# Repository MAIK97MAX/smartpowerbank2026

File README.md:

# Semesterproject 2026 - Smart Powerbank

## Authors
Jukic Malik & Sayfutdinov David - HTL Rankweil

## Goal 
The goal of this project is to design and build a smart power bank with USB-C charging, battery management and system monitoring.

## Features
- USB-C charging
- OLED display for battery status and system information
- ESP8266 module for web interface
- Battery monitoring and protection

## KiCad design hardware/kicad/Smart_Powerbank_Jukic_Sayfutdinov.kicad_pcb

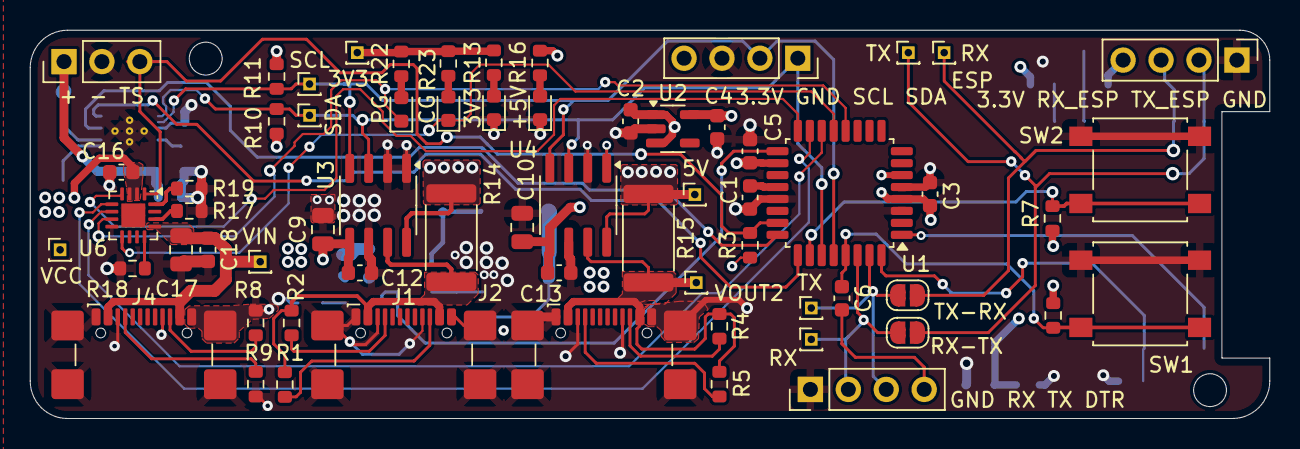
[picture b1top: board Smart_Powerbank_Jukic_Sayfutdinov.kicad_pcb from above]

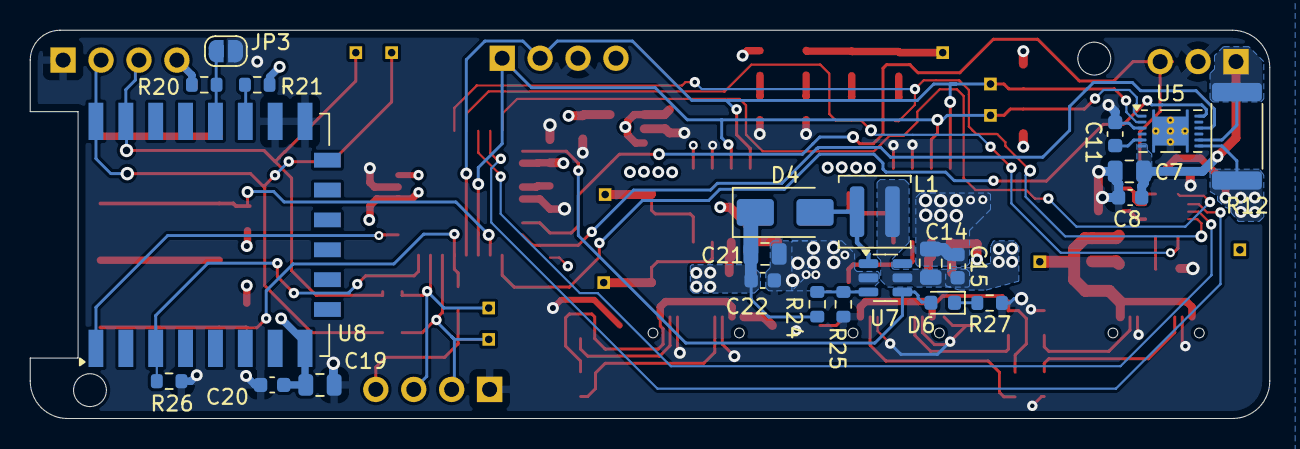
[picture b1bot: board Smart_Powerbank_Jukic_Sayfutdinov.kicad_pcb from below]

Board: 4 copper layers, 83.0 x 26.0 mm, 87 parts (23 on the bottom side), 48 nets.

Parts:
3.3V GND SCL SDA: Conn_01x04_Pin; PinSocket_1x04_P2.54mm_Vertical
3.3V RX_ESP TX_ESP GND: Conn_01x04_Pin; PinHeader_1x04_P2.54mm_Vertical
3V3: LED; LED_0603_1608Metric
3V3#2, 5V: TestPoint_Probe; PinHeader_1x01_P1.00mm_Vertical
+5V: LED; LED_0603_1608Metric
+ - TS: Conn_01x03_Pin; PinHeader_1x03_P2.54mm_Vertical
C1, C2, C3, C4, C5, C6, C8, C12, C13, C15, C18, C20, C22: 100nF; C_0603_1608Metric
C7, C17: 1uF; C_0805_2012Metric
C9, C10, C19: 10uF; C_0805_2012Metric
C11: 470nF; C_0603_1608Metric
C14, C21: 22uF; C_0805_2012Metric
C16: 4.7uF; C_0603_1608Metric
CG: LED; LED_0603_1608Metric
D4: D_Schottky; D_SMA
D6: n.b.; LED_0603_1608Metric
GND RX TX DTR: Conn_01x04_Pin; PinHeader_1x04_P2.54mm_Vertical
J1, J2, J4: USB_C_Receptacle_USB2.0_16P; USB_C_Receptacle_GCT_USB4110
JP3: SolderJumper_2_Open; SolderJumper-2_P1.3mm_Open_RoundedPad1.0x1.5mm
L1: 4.7uH; L_Coilcraft_XAL4030-XXX
PG: LED; LED_0603_1608Metric
R1, R2, R3, R4, R5, R6, R7, R20, R21: 10k; R_0603_1608Metric
R8, R9: 5k1; R_0603_1608Metric
R10, R11: 3.3k; R_0603_1608Metric
R12, R14, R15: 0.01; R_2512_6332Metric
R13, R16, R18, R19, R22, R23: 1k; R_0603_1608Metric
R17: 47k; R_0603_1608Metric
R24: 110k; R_0603_1608Metric
R25: 15k; R_0603_1608Metric
R26: 100k; R_0603_1608Metric
R27: n.b.; R_0603_1608Metric
RX: TestPoint_Probe; PinHeader_1x01_P1.00mm_Vertical
RX#2: TestPoint_Probe; PinHeader_1x01_P1.00mm_Vertical
RX-TX: SolderJumper_2_Open; SolderJumper-2_P1.3mm_Open_RoundedPad1.0x1.5mm
SCL: TestPoint_Probe; PinHeader_1x01_P1.00mm_Vertical
SDA: TestPoint_Probe; PinHeader_1x01_P1.00mm_Vertical
SW1, SW2: SW_Push; SW_SPST_B3S-1000
TX: TestPoint_Probe; PinHeader_1x01_P1.00mm_Vertical
TX#2: TestPoint_Probe; PinHeader_1x01_P1.00mm_Vertical
TX-RX: SolderJumper_2_Open; SolderJumper-2_P1.3mm_Open_RoundedPad1.0x1.5mm
U1: ATmega328-A; TQFP-32_7x7mm_P0.8mm
U2: AP2112K-3.3; SOT-23-5
U3, U4: INA219AxD; SOIC-8_3.9x4.9mm_P1.27mm
U5: BQ27441-G1; Texas_S-PDSO-N12
U6: BQ24074RGT; VQFN-16-1EP_3x3mm_P0.5mm_EP1.6x1.6mm
U7: MT3608; SOT-23-6
U8: ESP-12E
VCC: TestPoint_Probe; PinHeader_1x01_P1.00mm_Vertical
VIN: TestPoint_Probe; PinHeader_1x01_P1.00mm_Vertical
VOUT2: TestPoint_Probe; PinHeader_1x01_P1.00mm_Vertical

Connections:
+3.3V: 3.3V GND SCL SDA.4, 3.3V RX_ESP TX_ESP GND.4, 3V3#2.1, C3.1, C4.1, C5.1, C9.1, C10.1, C12.1, C13.1, C19.1, C20.1, R3.2, R6.2, R7.2, R10.1, R11.1, R13.2, R20.2, R21.2, R22.2, R23.2, U1.4 (VCC), U1.6 (VCC), U1.18 (AVCC), U2.5 (VOUT), U3.5 (VS), U4.1 (A1), U4.5 (VS), U8.8 (VCC)
+5V: 5V.1, C21.1, C22.1, D4.1 (K), R14.1, R15.1, R16.2, R24.1, U3.8 (IN+), U4.8 (IN+)
/AREF: C1.1, U1.20 (AREF)
/BAT+: + - TS.1, C7.1, C8.1, R12.1, U5.6 (BAT), U5.8 (SRP)
/BIN: U1.24 (PC1), U5.10 (BIN)
/CE: U1.16 (PB4), U6.4 (~CE)
/CHG: CG.1 (K), U1.13 (PB1), U6.9 (~CHG)
/DTR: C6.2, GND RX TX DTR.4
/EN1: U1.14 (PB2), U6.6 (EN1)
/EN2: U1.15 (PB3), U6.5 (EN2)
/EN_OUT: D6.2 (A), U1.17 (PB5), U7.4 (EN)
/ESP_EN: R26.1, U1.32 (PD2), U8.3 (EN)
/ESP_RST: U1.1 (PD3), U8.1 (~RST)
/FB: R24.2, R25.1, U7.3 (FB)
/GPOUT: U1.25 (PC2), U5.12 (GPOUT)
/ILIM: R18.2, U6.12 (ILIM)
/ISET: R19.1, U6.16 (ISET)
/PGOOD: PG.1 (K), U1.12 (PB0), U6.7 (~PGOOD)
/RST: C6.1, R6.1, SW1.1, U1.29 (~RESET/PC6)
/RX: GND RX TX DTR.2, RX.1, RX-TX.1 (A), U1.30 (PD0)
/RX_ESP: 3.3V RX_ESP TX_ESP GND.3, RX#2.1, TX-RX.2 (B), U8.21 (GPIO3/RXD)
/SCL: 3.3V GND SCL SDA.2, R11.2, SCL.1, U1.28 (PC5), U3.4 (SCL), U4.4 (SCL), U5.2 (SCL)
/SDA: 3.3V GND SCL SDA.1, R10.2, SDA.1, U1.27 (PC4), U3.3 (SDA), U4.3 (SDA), U5.1 (SDA)
/SW: D4.2 (A), L1.2, U7.1 (SW)
/SW_MODE: R7.1, SW2.1, U1.26 (PC3)
/TMR: R17.2, U6.14 (TMR)
/TS: + - TS.3, R3.1, U1.23 (PC0), U6.1 (TS)
/TX: GND RX TX DTR.3, TX#2.1, TX-RX.1 (A), U1.31 (PD1)
/TX_ESP: 3.3V RX_ESP TX_ESP GND.2, RX-TX.2 (B), TX.1, U8.22 (GPIO1/TXD)
/VDD: C11.1, U5.5 (V_{DD})
GND: 3.3V GND SCL SDA.3, 3.3V RX_ESP TX_ESP GND.1, 3V3.1 (K), +5V.1 (K), + - TS.2, C1.2, C2.2, C3.2, C4.2, C5.2, C7.2, C8.2, C9.2, C10.2, C11.2, C12.2, C13.2, C14.2, C15.2, C16.1, C17.2, C18.2, C19.2, C20.2, C21.2, C22.2, GND RX TX DTR.1, J1.A1 (GND), J1.A8 (SBU1), J1.A12 (GND), J1.B1 (GND), J1.B8 (SBU2), J1.B12 (GND), J1.S1 (SHIELD), J2.A1 (GND), J2.A8 (SBU1), J2.A12 (GND), J2.B1 (GND), J2.B8 (SBU2), J2.B12 (GND), J2.S1 (SHIELD), J4.A1 (GND), J4.A8 (SBU1), J4.A12 (GND), J4.B1 (GND), J4.B8 (SBU2), J4.B12 (GND), J4.S1 (SHIELD), JP3.1 (A), R8.1, R9.2, R17.1, R18.1, R19.2, R25.2, R26.2, R27.1, SW1.2, SW2.2, U1.3 (GND), U1.5 (GND), U1.21 (GND), U2.2 (GND), U3.1 (A1), U3.2 (A0), U3.6 (GND), U4.2 (A0), U4.6 (GND), U5.3 (V_{SS}), U5.13 (PAD), U6.8 (VSS), U6.17 (VSS), U7.2 (GND), U8.15 (GND), U8.16 (GPIO15)
unnamed: 3V3.2 (A), R13.1
unnamed: +5V.2 (A), R16.1
unnamed: PG.2 (A), R22.1
unnamed: CG.2 (A), R23.1
unnamed: D6.1 (K), R27.2
unnamed: J1.A5 (CC1), R2.1
unnamed: J1.B5 (CC2), R1.2
unnamed: J2.A5 (CC1), R5.1
unnamed: J2.B5 (CC2), R4.2
unnamed: J4.A5 (CC1), R9.1
unnamed: J4.B5 (CC2), R8.2
unnamed: JP3.2 (B), R20.1, U8.18 (GPIO0)
unnamed: R21.1, U8.17 (GPIO2)
VCC: C2.1, C14.1, C15.1, C16.2, L1.1, R12.2, U2.1 (VIN), U2.3 (EN), U5.7 (SRN), U6.2 (BAT), U6.3 (BAT), U7.5 (IN), VCC.1
VIN_USB: C17.1, C18.1, J4.A4 (VBUS), J4.A9 (VBUS), J4.B4 (VBUS), J4.B9 (VBUS), U6.13 (IN), VIN.1
VOUT1: J1.A4 (VBUS), J1.A9 (VBUS), J1.B4 (VBUS), J1.B9 (VBUS), R1.1, R2.2, R14.2, U3.7 (IN-)
VOUT2: J2.A4 (VBUS), J2.A9 (VBUS), J2.B4 (VBUS), J2.B9 (VBUS), R4.1, R5.2, R15.2, U4.7 (IN-), VOUT2.1

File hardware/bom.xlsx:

Reference | Qty | Value | Footprint
C1,C2,C3,C4,C5,C6,C8,C12,C13,C15,C18,C20,C22 | 13 | 100nF | Capacitor_SMD:C_0603_1608Metric
C7,C17 | 2 | 1uF | Capacitor_SMD:C_0805_2012Metric
C9,C10,C19 | 3 | 10uF | Capacitor_SMD:C_0805_2012Metric
C11 | 1 | 470nF | Capacitor_SMD:C_0603_1608Metric
C14,C21 | 2 | 22uF | Capacitor_SMD:C_0805_2012Metric
C16 | 1 | 4.7uF | Capacitor_SMD:C_0603_1608Metric
D1,D2,D3,D5 | 4 | LED | LED_SMD:LED_0603_1608Metric
D4 | 1 | D_Schottky | Diode_SMD:D_SMA
D6 | 1 | n.b. | LED_SMD:LED_0603_1608Metric
J1,J2,J4 | 3 | USB_C_Receptacle_USB2.0_16P | Connector_USB:USB_C_Receptacle_GCT_USB4110
J3,J7 | 2 | Conn_01x04_Pin | Connector_PinHeader_2.54mm:PinHeader_1x04_P2.54mm_Vertical
J5 | 1 | Conn_01x04_Pin | Connector_PinSocket_2.54mm:PinSocket_1x04_P2.54mm_Vertical
J6 | 1 | Conn_01x03_Pin | Connector_PinHeader_2.54mm:PinHeader_1x03_P2.54mm_Vertical
JP1,JP2,JP3 | 3 | SolderJumper_2_Open | Jumper:SolderJumper-2_P1.3mm_Open_RoundedPad1.0x1.5mm
L1 | 1 | 4.7uH | Inductor_SMD:L_Coilcraft_XAL4030-XXX
R1,R2,R3,R4,R5,R6,R7,R20,R21 | 9 | 10k | Resistor_SMD:R_0603_1608Metric
R8,R9 | 2 | 5k1 | Resistor_SMD:R_0603_1608Metric
R10,R11 | 2 | 3.3k | Resistor_SMD:R_0603_1608Metric
R12,R14,R15 | 3 | 0.01 | Resistor_SMD:R_2512_6332Metric
R13,R16,R18,R19,R22,R23 | 6 | 1k | Resistor_SMD:R_0603_1608Metric
R17 | 1 | 47k | Resistor_SMD:R_0603_1608Metric
R24 | 1 | 110k | Resistor_SMD:R_0603_1608Metric
R25 | 1 | 15k | Resistor_SMD:R_0603_1608Metric
R26 | 1 | 100k | Resistor_SMD:R_0603_1608Metric
R27 | 1 | n.b. | Resistor_SMD:R_0603_1608Metric
SW1,SW2 | 2 | SW_Push | Button_Switch_SMD:SW_SPST_B3S-1000
TP1,TP2,TP3,TP4,TP5,TP6,TP7,TP8,TP9,TP10,TP11,TP12 | 12 | TestPoint_Probe | Connector_PinHeader_1.00mm:PinHeader_1x01_P1.00mm_Vertical
U1 | 1 | ATmega328-A | Package_QFP:TQFP-32_7x7mm_P0.8mm
U2 | 1 | AP2112K-3.3 | Package_TO_SOT_SMD:SOT-23-5
U3,U4 | 2 | INA219AxD | Package_SO:SOIC-8_3.9x4.9mm_P1.27mm
U5 | 1 | BQ27441-G1 | Package_SON:Texas_S-PDSO-N12
U6 | 1 | BQ24074RGT | Package_DFN_QFN:VQFN-16-1EP_3x3mm_P0.5mm_EP1.6x1.6mm
U7 | 1 | MT3608 | Package_TO_SOT_SMD:SOT-23-6
U8 | 1 | ESP-12E | RF_Module:ESP-12E

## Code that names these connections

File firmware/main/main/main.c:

/*
 * main.c
 *
 * Created: 25.06.2026 22:47:29
 * Author : Malik
 */ 

#define F_CPU 8000000UL

#define INA_REG_SHUNT_V 0x01
#define INA_REG_BUS_V 0x02
#define INA_REG_CURRENT 0x04
#define INA_REG_CALIBRATION 0x05
#define INA_CALIBRATION 0x1000
#define INA1_W 0x80
#define INA1_R 0x81
#define INA2_W 0x88
#define INA2_R 0x89

#define BUTTON PC3

#include <avr/io.h>
#include <util/delay.h>
#include "molibdisplay.h"

//-----------------------------INA219---------------------------------//

uint16_t ina_read_reg(uint8_t addr_w, uint8_t addr_r, uint8_t reg)
{
	uint16_t value;

	if (!twi_s_start(addr_w))
	{
		twi_s_stop();
		return 0xFFFF;
	}

	if (!twi_s_write(reg))
	{
		twi_s_stop();
		return 0xFFFF;
	}

	if (!twi_s_rep_start(addr_r))
	{
		twi_s_stop();
		return 0xFFFF;
	}

	value = ((uint16_t)twi_s_read(ACK)) << 8;
	value |= twi_s_read(NACK);

	twi_s_stop();

	return value;
}

uint8_t ina_write_reg(uint8_t addr_w, uint8_t reg, uint16_t value) 
{
	if(!twi_s_start(addr_w)) 
	{
		twi_s_stop();
		return 0;
	}
	
	if(!twi_s_write(reg))
	{
		twi_s_stop();
		return 0;
	}
	
	if(!twi_s_write((uint8_t)(value >> 8)))
	{
		twi_s_stop();
		return 0;
	}
	
	if(!twi_s_write((uint8_t)value))
	{
		twi_s_stop();
		return 0;
	}
	
	twi_s_stop();
	
	return 1;
}

float ina_bus_voltage(uint8_t addr_w, uint8_t addr_r)
{
	uint16_t raw = ina_read_reg(addr_w, addr_r, INA_REG_BUS_V);

	raw >>= 3;              // Bits 15..3 enthalten die Busspannung
	return raw * 0.004;    // 4 mV pro Bit
}

int16_t ina_shunt_raw(uint8_t addr_w, uint8_t addr_r)
{
	return (int16_t)ina_read_reg(addr_w, addr_r, INA_REG_SHUNT_V);
}

int16_t ina_current(uint8_t addr_w, uint8_t addr_r)
{
	return (int16_t)ina_read_reg(addr_w, addr_r, INA_REG_CURRENT);
}

//-----------------------------init------------------------------//

void init() {
	DDRB |= (1 << PB5) | (1 << PB2) | (1 << PB3);
	PORTB |= (1 << PB5) | (1 << PB3);
	PORTB &= ~(1 << PB2);
	
	DDRC &= ~(1 << BUTTON);
	
	DDRC &= ~(1<<PC2);   // PC2 as input (GPOUT)
	DDRC  |=  (1<<PC1);  // PC1 as output (BIN)
	PORTC &= ~(1<<PC1);  // PC1 low = battery present
}

void ina_init()
{
	ina_write_reg(INA1_W, INA_REG_CALIBRATION, INA_CALIBRATION);
	ina_write_reg(INA2_W, INA_REG_CALIBRATION, INA_CALIBRATION);
	
	_delay_ms(1);
}

//-----------------------------MAIN------------------------------//

int main(void)
{	
	init();
	display_init();
	ina_init();
	
	uint8_t screen = 0;
	
	display_clear();

    while (1) 
    {   
		if (!(PINC & (1 << BUTTON)))
		{
			_delay_ms(30);

			if (!(PINC & (1 << BUTTON)))
			{
				screen ^= 1;

				while (!(PINC & (1 << BUTTON)))
				{
				}

				_delay_ms(30);
			}
		}
		
		float u1 = ina_bus_voltage(INA1_W, INA1_R);
		float u2 = ina_bus_voltage(INA2_W, INA2_R);
		
		int16_t i1 = ina_current(INA1_W, INA1_R);
		int16_t i2 = ina_current(INA2_W, INA2_R);
		
		if (screen == 0)
		{
			display_printf_pos(0, 0, "SmartPowerbank");
			display_printf_pos(0, 1, "HTL Rankweil");
			display_printf_pos(0, 3, "Malik Jukic &");
			display_printf_pos(0, 4, "David Sayfutdinov");
		} 
		else
		{
			display_clear();
			display_printf_pos(0, 0, "OUT1:%d.%02dV",
			(int)u1,
			((int)(u1 * 100)) % 100);

			display_printf_pos(0, 3, "OUT2:%d.%02dV",
			(int)u2,
			((int)(u2 * 100)) % 100);
			
			display_printf_pos(0,1, "I1:%dmA", i1);
			display_printf_pos(0,4, "I2:%dmA", i2);
			
			_delay_ms(1000);
		}		
    }
}

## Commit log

2026-03-09 added KiCAD-Files
2026-03-09 added Images directory
2026-03-09 del placeholder
2026-03-12 Finished component placement, i2c routing and uart routing
2026-04-09 edited docs
2026-04-09 finished atmega logic pin routing and revised power layout
2026-04-30 cleanup and prep for ordering
2026-04-30 Added mounting holes and fixed drc issues
2026-05-07 changed silkscreen labels and created gerbers
2026-05-07 made final changes; added gerbers.zip; orderd parts from inventory
2026-05-28 created .step file of board
2026-05-28 finished chapter 2.1; Added chapter 2.2 and 2.2.1
2026-06-23 created .stl file of board
2026-06-28 burned bootloader, added firmware for oled display and voltage/current meas
2026-06-28 finished firmware and report
2026-06-29 Add custom sponsorship URL
    Added a custom sponsorship URL to the FUNDING.yml file.
2026-06-29 Modify custom sponsorship URL format
